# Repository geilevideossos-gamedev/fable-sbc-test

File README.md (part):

# VoxHub CM4 - a Home Assistant voice hub with Claude inside

A single-board computer for home automation that runs **Home Assistant OS** and works as a
**Claude-based voice assistant**: it listens for a wake word, transcribes the request locally, lets Claude
answer and control the home through tool use, and speaks the reply.

**Two identical boards, one Home Assistant for the whole house.** Board 1, the **hub** (upstairs), runs Home
Assistant OS, the Zigbee coordinator and the Claude pipeline. Board 2, the **satellite** (downstairs), runs no Home
Assistant: it gives the hub its wake word, microphones, speaker, mute switch and LEDs over Wi-Fi, and its radio
runs Zigbee router firmware that extends the mesh to the ground floor. Every request of both devices goes through
Claude, knows which room it came from, and is answered on the speaker of the device that heard it.

Everything in this repository is generated from code - schematic, PCB, enclosure, OS image and add-on.

| | |
|---|---|
|  |  |
| carrier with CM4 + heat sink (component side) | enclosure, rear view: USB-C PD in, 2 x USB-A, microSD |

**Showcase animation (shows revision A1, not re-rendered for A2):** [`media/voxhub_showcase.mp4`](media/voxhub_showcase.mp4) (1080p60, 21 s: closed device, exploded
view, orbit, reassembly, turntable) - rendered with Blender from the STEP files of this repository, see [`media/`](media/README.md).

> **Status: revision A2, ready to order fully assembled from JLCPCB, not yet built.** Every part is in stock in
> JLCPCB's assembly library (checked live on 2026-11-12), ERC and DRC pass against JLCPCB's design rules, the order files
> are in [`fab/jlcpcb/`](fab/jlcpcb). Nothing has to be soldered by hand: order the boards, print the enclosure, plug in
> the CM4, screw it together. No hardware exists yet - read the "Open items" in [DECISIONS.md](DECISIONS.md) first.
>
> | Step | Document |
> |---|---|
> | 1. Order 5 PCBs, 2 of them assembled | [`fab/ORDER_GUIDE.md`](fab/ORDER_GUIDE.md) - every option to click, cost estimate |
> | 2. Buy everything that is not on the board | [`fab/SHOPPING_LIST.md`](fab/SHOPPING_LIST.md) - EU shops, part numbers, prices |
> | 3. Print, test, assemble, flash the radio | [`fab/ASSEMBLY_AND_TEST.md`](fab/ASSEMBLY_AND_TEST.md) |
> | 4. Hub + satellite: Claude pipeline, satellite SD card, pairing, rooms, Zigbee router, tests from both rooms | [`fab/ASSEMBLY_AND_TEST.md`, chapter 7](fab/ASSEMBLY_AND_TEST.md#7-two-devices-hub-and-satellite) |

## System overview

| Function | Implementation |
|---|---|
| Compute | Raspberry Pi **Compute Module 4 Lite, wireless** (BCM2711 4x A72, 4 GB) - official HAOS target `rpi4-64` |
| Wi-Fi / Bluetooth | on the CM4: 2.4 + 5 GHz 802.11ac, Bluetooth 5.0 |
| Storage | microSD (push-push socket, card power switched by the module) |
| USB | 2 x USB-A 2.0 host (stacked), USB2514B hub, 1.3 A current-limited per port, ESD protected |
| Microphones | 2 x Infineon IM69D130 PDM MEMS (bottom port), ADAU7002 PDM-to-I2S, hardware mute switch |
| Speaker | MAX98357A I2S class-D, 3.2 W into 4 ohm, JST-PH header, enclosed 3 W speaker with JST-PH plug in the enclosure |
| Zigbee / Thread | RF-star RF-BM-2652P2 (TI CC2652P, +20 dBm) on UART4, flashed from the CM4 with one command |
| Power | USB-C PD sink (CYPD3177): negotiates 9-20 V, then 5 V / 4 A buck (LMR33640) |
| UI | green + blue status LEDs, red mute LED (hard-wired), mute slider on top |
| PCB | 100 x 74 mm, 4 layers, 1.6 mm (JLC04161H-3313), parts on one side + mute switch and three status LEDs on the other |
| Enclosure | 158.8 x 79.2 x 28 mm, two printed parts, no supports |

### Block diagram

```mermaid
flowchart LR
    PD[USB-C PD charger<br/>9-20 V] --> J1[USB-C<br/>receptacle]
    J1 -->|VBUS| BCR[CYPD3177<br/>PD sink controller]
    J1 -->|VBUS| Q1[P-FET<br/>load switch]
    BCR -->|gate| Q1
    Q1 -->|VBUS_SW| BUCK[LMR33640<br/>5 V / 4 A buck]
    BUCK -->|+5V| CM4
    BUCK -->|+5V| SW[2 x TPS2553<br/>port switches]
    BUCK -->|+5V| AMP[MAX98357A<br/>class-D amp]

    subgraph CM4[Raspberry Pi CM4 Lite wireless]
        SOC[BCM2711 + RAM]
        WIFI[Wi-Fi 2.4/5 GHz + BT 5.0]
    end
    CM4 -->|+3V3, 600 mA| LOADS[hub, SD, radio, mics]

    CM4 <-->|SDIO| SD[microSD]
    CM4 <-->|USB 2.0, nEXTRST| HUB[USB2514B hub]
    HUB <--> USBA[2 x USB-A]
    SW -->|VBUS 1.3 A| USBA

    MIC[2 x IM69D130<br/>PDM mics] -->|PDM| ADAU[ADAU7002<br/>PDM to I2S]
    ADAU -->|I2S data| MUTE{{mute switch}}
    MUTE -->|GPIO20| CM4
    CM4 -->|I2S GPIO18/19/21| AMP
    AMP --> SPK[speaker 4 ohm / 3 W]

    CM4 <-->|UART4, boot strap,<br/>reset, JTAG| ZB[RF-BM-2652P2<br/>Zigbee / Thread]
    CM4 -->|GPIO5/6| LED[status LEDs]
    CM4 <-->|I2C1| BCR
```

### Voice pipeline (hub + satellite)

```mermaid
flowchart LR
    subgraph SAT[satellite, downstairs]
        M2[microphones] --> W2[wake word<br/>microWakeWord]
        P2[speaker]
    end
    subgraph HUB[hub, upstairs: Home Assistant OS]
        M1[microphones] --> W1[wake word<br/>microWakeWord]
        P1[speaker]
        S[STT<br/>Whisper, local] -->|text + area of the device| C[Claude<br/>Anthropic integration]
        C <-->|Assist API: intents,<br/>exposed entities| HA[Home Assistant Core]
        G[VoxHub exposure guard:<br/>no locks, no alarms] -.-> HA
        C -->|text, streamed| T[TTS<br/>Piper, local]
    end
    W1 -->|audio after the wake word| S
    W2 -->|ESPHome API, Wi-Fi| S
    T -->|answer| P1
    T -->|answer URL| P2
```

Both devices run Linux Voice Assistant 1.1.18 (`assistant/voxhub_satellite` on the hub, `os/satellite` on the
satellite). Audio stays in the house; only the transcribed request, Claude's instructions, the names and areas of
the devices you expose and the results of Claude's tool calls go to Anthropic. The single-device VoxHub Assistant add-on
of revision A2 still exists for a hub without a satellite (`assistant/README.md`).

### GPIO map (CM4)

| GPIO | Function | Notes |
|---|---|---|
| 2 / 3 | I2C1 SDA / SCL | CYPD3177 PD controller (HPI, 0x08) |
| 5 / 6 | LED green / blue enable | active high, N-FET drivers, 10k pull-downs |
| 8 / 9 | UART4 TX / RX | radio module DIO12 (RX) / DIO13 (TX), 115200 baud, no flow control |
| 10 / 11 | UART4 CTS / RTS | wired to DIO18 / DIO19, not used by the standard firmware |
| 7 / 17 | JTAG TDI / TDO of the radio | DIO17 / DIO16, recovery flashing only |
| 14 / 15 | UART0 TX / RX | debug header (DNP) |
| 16 | amplifier SD_MODE | high = on (left channel) |
| 18 / 19 / 20 / 21 | I2S BCLK / LRCLK / DIN / DOUT | DIN passes through the mute switch |
| 22 / 23 | JTAG TMS / TCK of the radio | recovery flashing only |
| 24 / 25 | radio reset / boot-loader strap | GPIO24 **high = reset** (open-drain FET on RESET, 100k pull-down); GPIO25 low at reset = ROM serial boot loader (DIO15, 2.2k pull-up) |
| 27 | mute sense | high = muted |

## Power budget

5 V rail (buck output 5.02 V nominal, 4.86 .. 5.17 V over tolerance: Vref +-1.5 %, two 1 % resistors), worst case =
everything at its maximum simultaneously:

| Load | Typical | Peak | Basis |
|---|---|---|---|
| CM4 (SoC, RAM, Wi-Fi) | 3.5 W | 7.0 W | CM4 datasheet: 1.4 A typical maximum at 5 V |
| 3.3 V loads via the CM4 regulator (hub 70/150 mA, microSD 50/200 mA, radio 10/85 mA, mics + converter 3 mA, pull-ups 5 mA) | 0.14 A -> 0.5 W | 0.44 A -> 1.6 W | 3.3 V budget 600 mA; 90 % converter efficiency; radio: CC2652P at +20 dBm |
| USB-A ports | 0.5 W | 5.0 W | 2 x 500 mA (hardware limit 1.3 A per port) |
| Speaker amplifier | 0.3 W | 3.6 W | 3.2 W output at 90 % efficiency; speech averages far less |
| LEDs, pull-ups | 0.05 W | 0.1 W | |
| **5 V rail total** | **4.9 W (0.98 A)** | **17.3 W (3.45 A)** | buck rated 4 A |
| Buck + switch losses | 0.5 W | 1.9 W | 92 % at 9 V in, P-FET 70 mOhm, inductor 54 mOhm |
| **At the USB-C connector** | **5.4 W** | **19.2 W** | 9 V: 0.6 A typ / 2.13 A peak - 20 V: 0.27 A typ / 0.96 A peak |

- The PD controller requests **>= 2 A at 9-20 V** (18 W at 9 V). Realistic operation (no bus-powered disks, speech
  rather than sine waves) stays below 12 W. The theoretical simultaneous peak of 19.2 W exceeds an 18 W contract by 7 %:
  use a **27 W or larger** charger (9 V/3 A, or anything offering 12/15/20 V at >= 2 A) if both USB ports feed
  500 mA devices.
- 3.3 V budget: 440 mA peak of the 600 mA the CM4 can supply.
- Chargers without a 9-20 V PD profile are rejected safely: the load switch stays open, the buck stays in UVLO (< 7 V)
  and the red PD-FAULT LED lights.

## Thermal estimate (SoC)

Assumptions: 25 C room, module mounted component-side down in the vented enclosure, 14 x 14 x 7 mm heat sink on the BCM2711
(36 K/W on its own in free convection), heat also spreading through the module PCB and the two mezzanine connectors.
Effective module-level thermal resistance derived from published CM4 measurements (bare module on the IO board:
~25 K rise idle at ~2 W, ~55-60 K at full load): about **12 K/W bare, ~9.5-10 K/W with the heat sink in this enclosure**.

| Operating point | Module power | Estimated SoC temperature | Comment |
|---|---|---|---|
| Idle (HAOS, add-ons idle) | 2.0 W | 25 + 2.0 x 10 = **45 C** | |
| Voice assistant active (wake word on one core, Whisper bursts) | 3.5 W | **60 C** | normal operation |
| All four cores loaded continuously | 6.5 W | 90 C -> **throttles at 80 C** | firmware limits to roughly 5.5 W; only during updates / long local STT |

Conclusion: fine without a fan for the intended workload (LLM in the cloud). For sustained local inference fit the taller
15 x 15 x 9.5 mm heat sink (there are 12.9 mm between the SoC and the base plate, so about 3 mm stay free under it) or add a 30 mm fan to the base vents.
Other parts at peak load: buck IC ~1.1 W (junction about +45 K), inductor 0.7 W, P-FET 0.33 W - all uncritical.
These are estimates, not measurements - verify with `vcgencmd measure_temp` on the first prototype.

## Repository layout

| Path | Contents |
|---|---|
| [`hardware/`](hardware/README.md) | KiCad 9 project (generated), generator scripts, schematic PDF, BOM, Gerbers, drill, pick-and-place, DXF, renders, fab + assembly notes |
| [`fab/`](fab/ORDER_GUIDE.md) | JLCPCB order package (`jlcpcb/`: Gerbers, BOM, CPL, placement report), order guide, shopping list, assembly and test guide |
| [`tools/`](tools/flash_zigbee.sh) | `flash_zigbee.sh --role hub\|satellite`: writes the Zigbee coordinator (hub), the Zigbee router (satellite) or the Thread firmware to the radio module from the CM4; `test/`: radio simulator and test runner |
| [`enclosure/`](enclosure/README.md) | parametric CadQuery source, STL / 3MF / STEP, renders |
| [`os/`](os/README.md) | HAOS board definition, device tree overlay, `build-image.sh` (hub); [`os/satellite/`](os/satellite/README.md): SD card image of the satellite |
| [`assistant/`](assistant/README.md) | Home Assistant add-ons: **VoxHub Satellite** (hub side of the two-device system, exposure guard) and **VoxHub Assistant** (single device) |
| [`media/`](media/README.md) | showcase animation (MP4), still of the exploded view, Blender script and helpers |
| [`DECISIONS.md`](DECISIONS.md) | every design decision with its reasoning, the datasheet verification table, sourcing decisions, open items |
| [`TODO.md`](TODO.md) | progress checklist |

## How to build everything

Prerequisites: Linux, Python >= 3.10, `zip`, Java >= 21 (only for re-running the autorouter), `xvfb` for the
enclosure renders (`sudo apt install zip xvfb`), and KiCad 9 either as the Docker image `kicad/kicad:9.0` or installed
natively (`KICAD_NATIVE=1`; the Python that imports `pcbnew` also needs `numpy` and `shapely`).

```bash
# 1. Hardware: schematic -> ERC -> netlist -> placement -> autoroute -> DRC -> fabrication outputs -> fab/jlcpcb
docker pull kicad/kicad:9.0             # or: export KICAD_NATIVE=1
SKIP_ROUTE=1 hardware/build.sh all      # re-uses the checked-in autorouter session (reproduces the committed board, ~4 min)
# to autoroute again: wget -P hardware https://github.com/freerouting/freerouting/releases/download/v2.0.1/freerouting-2.0.1.jar
#                     hardware/build.sh all
# to refresh stock and prices: python3 hardware/gen/jlc_lookup.py refresh hardware/gen/sourcing_jlc.json

# 2. Enclosure: STL / 3MF / STEP + renders
pip install cadquery
python3 enclosure/voxhub_enclosure.py enclosure
xvfb-run -a python3 enclosure/render.py

# 3. OS image (latest official HAOS + VoxHub configuration)
sudo apt install git curl xz-utils fdisk mtools device-tree-compiler
os/build-image.sh repack --wifi-ssid "MyWifi" --wifi-psk "secret"
#    -> os/output/haos_voxhub-cm4-<version>.img.xz

# 3b. Satellite image (Raspberry Pi OS Lite + Linux Voice Assistant, about 30 minutes)
sudo apt install qemu-user-static binfmt-support parted e2fsprogs openssl
sudo os/satellite/build-satellite-image.sh --wifi-ssid "MyWifi" --wifi-psk "secret-password" --hub 192.168.1.10 --room Downstairs
#    -> os/output/voxhub-satellite-2026-10-06-lva1.1.18.img.xz

# 4. Add-ons: tests (VoxHub Satellite and VoxHub Assistant), container test of VoxHub Satellite (Docker)
pip install -r assistant/requirements-dev.txt
(cd assistant && python3 -m pytest -q)
assistant/tests/container/run_addon_test.sh

# 4b. Radio flashing script against the simulated radio (about 17 minutes)
sudo apt install python3-serial python3-intelhex
sudo tools/test/run_flash_tests.sh

# 5. Showcase animation (Blender 4.2 - 4.5, headless; a little over 3 hours on 4 CPU cores)
pip install cadquery pymupdf pillow numpy && sudo apt install ffmpeg
BLENDER=/path/to/blender media/build_showcase.sh
```

Then: order the boards (`fab/ORDER_GUIDE.md`), buy the rest (`fab/SHOPPING_LIST.md`), print `enclosure/voxhub_shell.3mf` and
`voxhub_base.3mf`, test and assemble (`fab/ASSEMBLY_AND_TEST.md`), flash the image, flash the radio (`tools/flash_zigbee.sh`),
add this repository as an add-on repository in Home Assistant (until the two-device version is merged into `main`:
`https://github.com/geilevideossos-gamedev/fable-sbc-test#claude/gallant-hamilton-kojnjj`) and install **VoxHub
Satellite**; for the second board
write the satellite image and follow `fab/ASSEMBLY_AND_TEST.md`, chapter 7.

## Cost summary

**Parts on the board**, JLCPCB prices of 2026-11-12 (USD, without tax, PCB, assembly fees and shipping).
Line by line: [`hardware/outputs/bom.csv`](hardware/outputs/bom.csv).

| Group | Lines | Placements | 1 board | per board at 100 |
|---|---|---|---|---|
| ICs and radio module (RF-BM-2652P2 alone: 6.63 / 5.56) | 8 | 11 | 20.85 | 15.11 |
| Connectors, slide switch, SMT spacers | 7 | 11 | 10.44 | 7.48 |
| Inductor, crystal, microphones | 3 | 4 | 6.48 | 4.23 |
| Capacitors | 11 | 49 | 2.78 | 2.21 |
| Diodes, LEDs, transistors | 9 | 14 | 1.18 | 0.96 |
| Resistors | 15 | 47 | 0.03 | 0.03 |
| **PCB assembly parts** | **53 (+2 DNP)** | **136** | **41.78** | **30.03** |

**Everything else for one device**, EU shops, prices of 2026-11-12 including VAT (EUR).
Line by line: [`hardware/outputs/bom_system.csv`](hardware/outputs/bom_system.csv) and [`fab/SHOPPING_LIST.md`](fab/SHOPPING_LIST.md).

| Item | EUR |
|---|---|
| Raspberry Pi CM4 Lite 4 GB wireless (CM4104000) | 105.83 |
| microSD card 64 GB, endurance type | 28.90 |
| USB-C PD charger 30 W and cable | 22.38 |
| Speaker with JST-PH plug, heat sink, screws, feet, foam | 18.39 |
| Shipping of two parcels to Austria | 12.90 |
| **One device without the board** | **188.40** |

**Hub + satellite** (the satellite with a 1 GB module, CM4101000, 50.82 EUR, and a 32 GB card): **286.90 EUR**
delivered for both devices without the boards, 66.01 EUR less than two hubs - [`fab/SHOPPING_LIST.md`, section
8](fab/SHOPPING_LIST.md#8-two-device-system-satellite-variant-and-combined-basket-hub--satellite).

**The JLCPCB order** (5 PCBs, 2 of them assembled on both sides, parts, shipping, import VAT) is estimated in
[`fab/ORDER_GUIDE.md`](fab/ORDER_GUIDE.md).

- The same JLCPCB parts cost 41.78 USD where the DigiKey parts of revision A1 cost 74.79 USD; the radio module alone
  went from 11.47 to 6.63 USD.
- Thin stock at JLCPCB on the day of the check: ADAU7002ACBZ-R7 (104), Wurth 61400826021 (116), RF-BM-2652P2 (126).
  The order guide says how to reserve them; the BOM names the alternates. Details in
  [DECISIONS.md, section 10](DECISIONS.md#10-sourcing-jlcpcb--lcsc-live-check-2026-11-12-digikey-2026-11-11-as-the-second-source).
- In a Standard PCBA order JLCPCB charges the same feeder fee for every part type, Basic or Extended, so the 32 Extended
  lines cost nothing extra compared with Basic parts; what counts is the number of BOM lines (53).

## Verification summary

| Check | Result | Evidence |
|---|---|---|
| ERC (kicad-cli 9.0.9) | 0 errors, 0 warnings | `hardware/outputs/erc.rpt` |
| Netlist equals the code model | 150 components / 100 nets; schematic parity 0 issues | `hardware/gen/model_netlist.json`, `hardware/outputs/drc.rpt` |
| DRC with schematic parity and JLCPCB's rules (kicad-cli 9.0.9) | 0 violations, 0 unconnected pads, 0 parity issues; two library-comparison checks waived (5 warnings, explained in `hardware/README.md`) | `hardware/outputs/drc.rpt`, `drc_waived_checks_enabled.rpt`, `hardware/voxhub.kicad_dru` |
| Current paths | narrowest copper of every high-current path measured: all as wide as designed (1.2 to 1.6 mm; the remaining necks are the 0.6 mm pads of the connector and of the regulator) | `hardware/outputs/power_paths.txt` |
| Vias and pads | no via in or touching a pad other than the exposed pad of an IC | `hardware/outputs/via_in_pad.txt` |
| USB 2.0 | upstream pair coupled, 0.14 / 0.16 mm = 89.96 ohm in JLCPCB's impedance calculator; pad-to-pad skew 0.00 / 0.00 / 0.00 mm (upstream / port 1 / port 2), limit 3.8 mm; no vias, no stubs | `hardware/outputs/usb_impedance.txt`, `routing_stats.txt`, DECISIONS.md section 6a |
| CM4 socket strips | no copper of another net in Hirose's restricted strips | `hardware/outputs/df40_strips.txt` |
| Assembly data | 135 of 136 placements fitted to JLCPCB's own footprint of the part (position, rotation, polarity); the last one is the hand-soldered USB-A connector | `fab/jlcpcb/placement_report.csv` |
| Parts vs. datasheets | 34 rows: 31 "verified against datasheet" with source (seven of them still read from distributor copies of the manufacturer PDF), 2 rows with shop dimensions only (speaker, heat sink), 1 row of generic passives / standard footprints not individually verified | `DECISIONS.md` section 9 and decision logs |
| PCB render | kicad-cli 3D renders | `hardware/outputs/render_*.png` |
| Enclosure fit | part dimensions from the manufacturer drawings; 0 mm^3 interference PCB assembly vs. printed parts | `enclosure/voxhub_enclosure.py`, `enclosure/README.md` |
| Power budget / thermal estimate | above | |
| Sourcing | every BOM line in stock in JLCPCB's assembly library on 2026-11-12 (three lines below 200 pieces); DigiKey data of 2026-11-11 as the second source | `hardware/outputs/bom.csv`, `hardware/gen/sourcing_jlc.json` |
| Radio flashing | one command; run end to end against a simulated radio with the real flashing tool, dry run in this repository; not on hardware | `tools/flash_zigbee.sh`, `fab/ASSEMBLY_AND_TEST.md` |
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
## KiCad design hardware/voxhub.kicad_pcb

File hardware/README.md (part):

# Hardware: VoxHub CM4 carrier, revision A2

KiCad 9 project, **generated entirely from code** (`gen/`). Do not edit the `.kicad_sch` / `.kicad_pcb` files
by hand - change the generator and run `./build.sh`.

Revision A2 is the revision that is ordered fully assembled from JLCPCB. The order files are in
[`../fab/jlcpcb/`](../fab/jlcpcb), the ordering steps in [`../fab/ORDER_GUIDE.md`](../fab/ORDER_GUIDE.md), what changed
from A1 and why in the A2 log of [`../DECISIONS.md`](../DECISIONS.md).

## Contents

| Path | What |
|---|---|
| `voxhub.kicad_pro`, `voxhub.kicad_sch` + 5 sub-sheets, `voxhub.kicad_pcb` | the KiCad project |
| `voxhub.kicad_dru` | JLCPCB limits that KiCad's board setup cannot express (component holes, pad to pad) |
| `voxhub.kicad_sym`, `voxhub.pretty/` | project symbol / footprint libraries (generated) |
| `3dmodels/` | STEP models used by the footprints (KiCad library copies + simple stand-ins) |
| `gen/design.py` | **the circuit**: every part, value and net |
| `gen/kisch.py`, `gen/sexpr.py` | schematic writer |
| `gen/parts.py` | part catalogue: one entry per purchasable part |
| `gen/jlc_lookup.py`, `gen/sourcing_jlc.json`, `gen/jlc_footprints.json` | live lookups in JLCPCB's assembly library and at LCSC; the stored result (LCSC number, library type, stock, prices); JLCPCB's own footprints of every part |
| `gen/sourcing.py`, `gen/sourcing_live.json`, `gen/make_bom.py` | second sources, DigiKey data of 2026-11-11, system parts with their EU shop, BOM generator |
| `gen/make_footprints.py`, `gen/make_3dmodels.py` | project footprints and coloured stand-in models |
| `gen/prewire.py` | **hand-designed copper**: PD input, load switch, buck stage, USB port supplies, all six USB data lines; stack-up and USB geometry |
| `gen/build_pcb.py` | placement, silkscreen legends, pre-wired copper, power fan-out, keep-outs, DSN export, import, patch router, repair, USB length measurement |
| `gen/postroute.sh` | iterate DRC -> repair -> patch until clean |
| `gen/check_power.py`, `gen/check_df40.py`, `gen/check_vias.py` | build gates: narrowest copper of the high-current paths; foreign copper in the CM4 socket strips; vias in or touching a pad |
| `gen/jlc_impedance.py` | asks JLCPCB's impedance calculator for the USB geometry |
| `gen/make_jlc.py` | JLCPCB BOM, CPL and placement report |
| `gen/routed/voxhub.ses` | autorouter session (Freerouting 2.0.1) the committed board was built from |
| `gen/placement.json` | final part positions (also drives the enclosure model) |
| `outputs/` | reports and fabrication data (below) |

### `outputs/`

| File | Purpose |
|---|---|
| `voxhub_schematic.pdf` | schematic, 6 pages |
| `erc.rpt`, `drc.rpt` | kicad-cli reports: **0 ERC violations, 0 DRC violations, 0 unconnected, 0 parity issues** |
| `drc_waived_checks_enabled.rpt` | the same DRC with the two waived checks switched on (5 warnings, explained below) |
| `power_paths.txt` | narrowest copper of every high-current path against its requirement |
| `df40_strips.txt` | copper inside Hirose's restricted strips of the CM4 sockets (own net / other net) |
| `via_in_pad.txt` | vias whose land overlaps an SMD pad (allowed only inside the exposed pad of an IC) |
| `usb_impedance.txt` | USB track geometry in JLCPCB's impedance calculator |
| `routing_stats.txt` | track / via counts; USB lines: pad-to-pad length and skew, the pads each line runs through, copper that is not on that path; SD / I2S / PDM lengths |
| `gerbers/` + `voxhub_gerbers.zip` | Gerbers with Protel extensions: F / In1 / In2 / B copper, mask, paste, silk, Edge.Cuts; Excellon PTH + NPTH drill, drill maps, job file (`../fab/jlcpcb/gerbers.zip` is the same set without maps and job file) |
| `voxhub_pos.csv` | pick-and-place as KiCad exports it (both sides, DNP parts excluded); for JLCPCB use `../fab/jlcpcb/cpl_jlcpcb.csv` |
| `bom.csv`, `bom_summary.json` | PCB assembly BOM: MPN, LCSC number, JLCPCB library type, JLCPCB and LCSC stock, JLCPCB prices at 1 / 10 / 100 (live, 2026-11-12), DigiKey second source (2026-11-11), other alternates |
| `bom_system.csv` | module, speaker, heat sink, screws, SD card, charger with EU shop and price |
| `voxhub_outline.dxf`, `mechanical_positions.csv` | mechanical outline: board edge, mounting holes, CM4 holes / outline, microphone ports, connector envelopes |
| `voxhub_pcb.step` | 3D model of the assembled board |
| `pcb_layers/voxhub.pdf` | layer plots |
| `render_top.png`, `render_bottom.png`, `render_iso.png` | kicad-cli 3D renders |

## Rebuilding

```bash
docker pull kicad/kicad:9.0                # KiCad 9.0.9 was used
wget -P hardware https://github.com/freerouting/freerouting/releases/download/v2.0.1/freerouting-2.0.1.jar
SKIP_ROUTE=1 hardware/build.sh all         # schematic -> ERC -> netlist -> place -> import -> patch -> DRC -> outputs -> fab/jlcpcb
hardware/build.sh all                      # same, but re-runs the autorouter first (Java >= 21)
```

Single steps: `hardware/build.sh sch | pcb | route | outputs`.

| Environment variable | Meaning |
|---|---|
| `KICAD_IMAGE` | Docker image with KiCad 9 (default `kicad/kicad:9.0`). `shapely` is installed into the container with pip when it is missing |
| `KICAD_NATIVE=1` | use `kicad-cli` and `pcbnew` of the host instead of Docker. The build picks the first of `$KICAD_PYTHON`, `python3`, `python3.12`, `python3.11` that imports `pcbnew`, `numpy` and `shapely` |
| `FREEROUTING` | path of the Freerouting jar (default `hardware/freerouting-2.0.1.jar`) |
| `SKIP_ROUTE=1` | re-use the committed autorouter session |

The host needs `python3` and `zip` (the archives are packed on the host; the script checks for `zip` first), and
`docker` unless `KICAD_NATIVE=1` is set.

`SKIP_ROUTE=1` re-uses the committed autorouter session and reproduces the committed board exactly (the patch
router is deterministic). Freerouting 2.0.1 with one thread produced the same session in every run here, but that is not
guaranteed on another machine or JRE. Two quirks the build works around: it sometimes exits with an empty session file
after routing (the build starts it up to three times and checks the file), and it keeps a `freerouting.json` in the
temp directory (each run gets its own).

Scripts that are run by hand:

| Command | What it does |
|---|---|
| `python3 gen/jlc_lookup.py refresh gen/sourcing_jlc.json` | reads stock, library type and prices of every BOM line live from JLCPCB and LCSC |
| `python3 gen/jlc_lookup.py footprints gen/sourcing_jlc.json gen/jlc_footprints.json` | fetches JLCPCB's footprint of every LCSC part (needed after a part change) |
| `python3 gen/jlc_lookup.py search "<keyword>"`, `... code C12345` | search the assembly library; full record of one part |
| `python3 gen/jlc_impedance.py outputs/usb_impedance.txt` | USB geometry of `prewire.py` in JLCPCB's impedance calculator |
| `python3 gen/check_power.py voxhub.kicad_pcb outputs/power_paths.txt` | current-path widths (run by `build.sh outputs`) |
| `python3 gen/check_df40.py voxhub.kicad_pcb outputs/df40_strips.txt` | CM4 socket strips (run by `build.sh outputs`) |
| `python3 gen/check_vias.py voxhub.kicad_pcb outputs/via_in_pad.txt` | vias against pads (run by `build.sh outputs`) |
| `python3 gen/make_jlc.py voxhub.kicad_pcb gen/sourcing_jlc.json gen/jlc_footprints.json ../fab/jlcpcb` | JLCPCB BOM, CPL, placement report (run by `build.sh outputs`) |

How the board is produced:

1. `design.py` writes the schematic; `kicad-cli sch erc` must pass; the KiCad netlist is compared pin by pin with the code model.
2. `build_pcb.py place`: fixed positions for connectors / ICs / mechanics and for the hand-placed power stage and USB parts,
   a greedy "nearest free spot to the pad it talks to" placer for the other passives; outline; keep-outs; silkscreen
   legends by an occupancy search; then the **pre-wired copper of `prewire.py`** (locked), the scripted fan-out of the
   remaining GND / +5V pads to the inner planes (never a via in or touching a lead pad), the fixed escape pattern of the
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
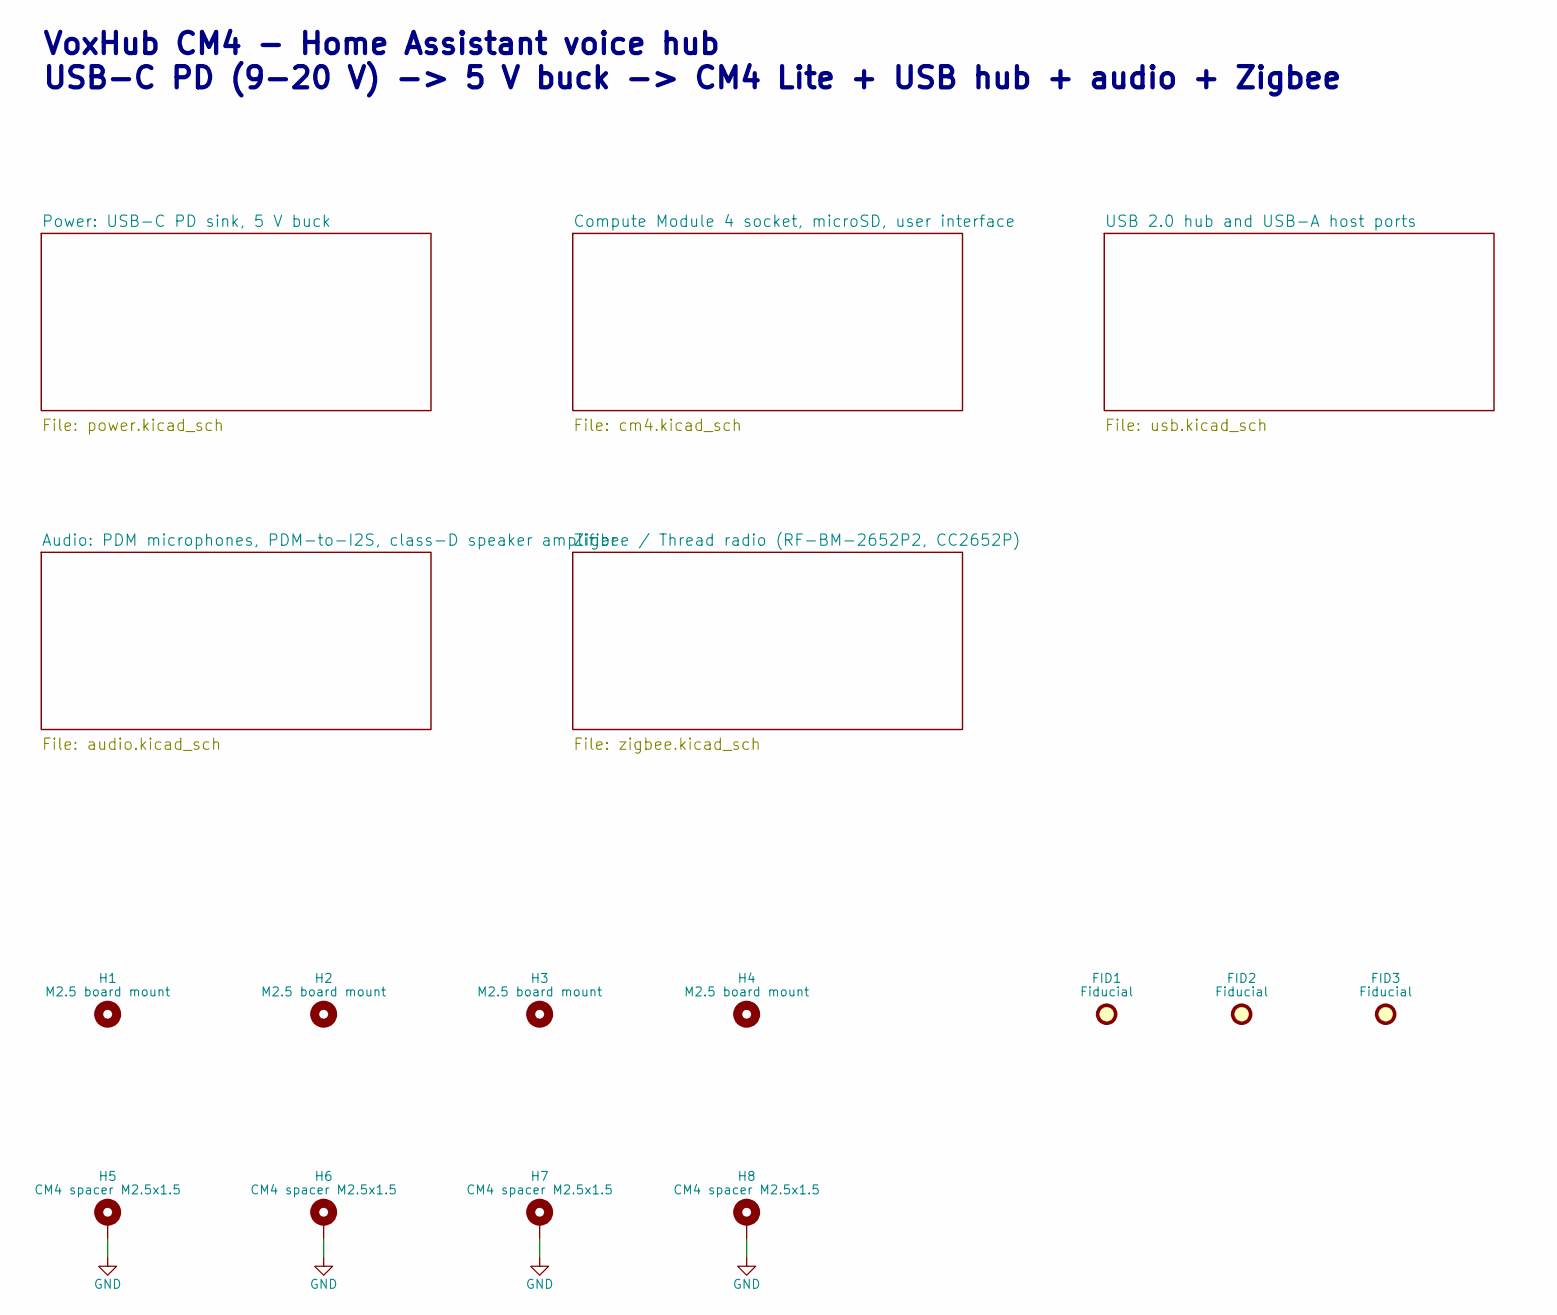
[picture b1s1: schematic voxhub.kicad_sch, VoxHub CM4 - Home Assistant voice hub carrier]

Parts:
FID1, FID2, FID3: Fiducial; Fiducial_1mm_Mask2mm; PartDescription Fiducial
H1, H2, H3, H4: M2.5 board mount; MountingHole_2.7mm_M2.5; PartDescription PCB mounting hole
H5, H6, H7, H8: CM4 spacer M2.5x1.5; Mounting_Wuerth_WA-SMSI-M2.5_H1.5mm_9774015151; MPN 9774015151R

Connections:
GND: H5.1, H6.1, H7.1, H8.1; also elsewhere on the board

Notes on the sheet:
VoxHub CM4 - Home Assistant voice hub USB-C PD (9-20 V) -> 5 V buck -> CM4 Lite + USB hub + audio + Zigbee

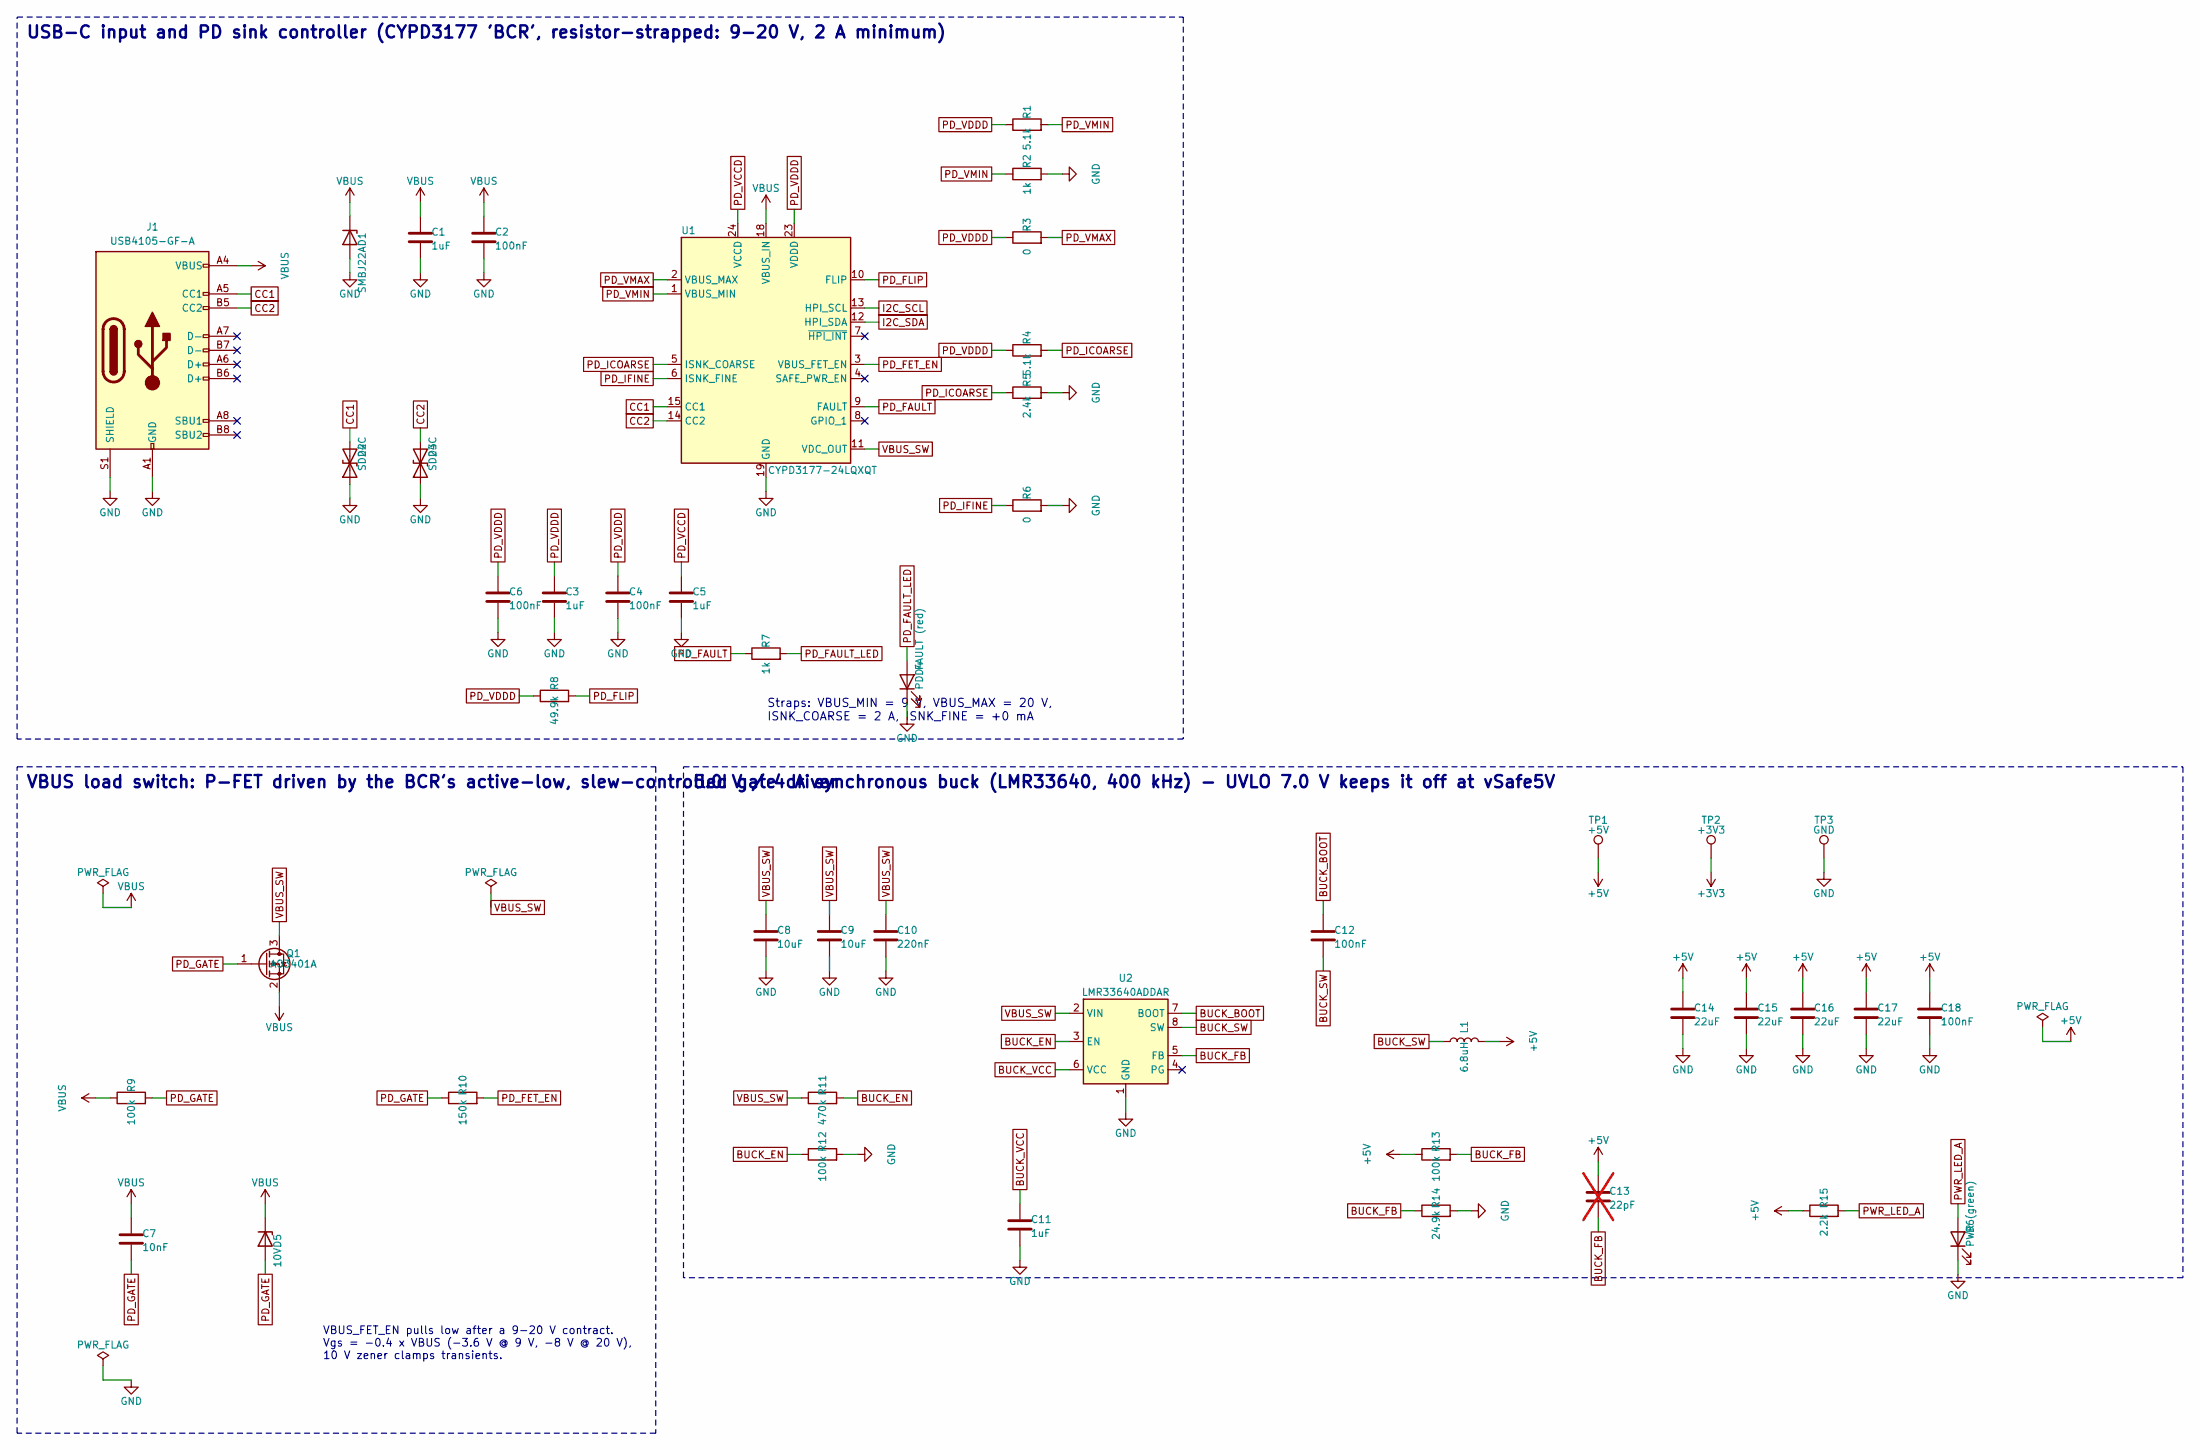
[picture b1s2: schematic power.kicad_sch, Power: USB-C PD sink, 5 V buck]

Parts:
C1: 1uF; C_0603_1608Metric; MPN CL10A105KB8NNNC
C2: 100nF; C_0603_1608Metric; MPN CC0603KRX7R9BB104
C3, C5, C11: 1uF; C_0603_1608Metric; MPN CL10B105KA8NNNC
C4, C6, C12, C18: 100nF; C_0402_1005Metric; MPN CL05B104KO5NNNC
C7: 10nF; C_0402_1005Metric; MPN CL05B103KB5NNNC
C8, C9: 10uF; C_1206_3216Metric; MPN CL31B106KBHNNNE
C10: 220nF; C_0603_1608Metric; MPN GRM188R71H224KAC4D
C13: 22pF; C_0402_1005Metric; MPN 0402CG220J500NT; not fitted
C14, C15, C16, C17: 22uF; C_1206_3216Metric; MPN CL31A226KAHNNNE
D1: SMBJ22A; D_SMB; MPN SMBJ22A
D2, D3: SD24C; D_SOD-323; MPN SD24C-01FTG
D4: PD FAULT (red); LED_0603_1608Metric; MPN LTST-C191KRKT
D5: 10V; D_SOD-323; MPN MM3Z10VT1G
D6: PWR (green); LED_0603_1608Metric; MPN 150060VS75000
J1: USB4105-GF-A; USB_C_Receptacle_GCT_USB4105-xx-A_16P_TopMnt_Horizontal; MPN USB4105-GF-A
L1: 6.8uH; L_Bourns_SRP7028A_7.3x6.6mm; MPN SLO0630H6R8MTT
Q1: AO3401A; SOT-23; MPN AO3401A
R1, R4: 5.1k; R_0402_1005Metric; MPN 0402WGF5101TCE
R2, R7: 1k; R_0402_1005Metric; MPN 0402WGF1001TCE
R3, R6: 0; R_0402_1005Metric; MPN 0402WGF0000TCE
R5: 2.4k; R_0402_1005Metric; MPN 0402WGF2401TCE
R8: 49.9k; R_0402_1005Metric; MPN 0402WGF4992TCE
R9, R12, R13: 100k; R_0402_1005Metric; MPN 0402WGF1003TCE
R10: 150k; R_0402_1005Metric; MPN 0402WGF1503TCE
R11: 470k; R_0402_1005Metric; MPN 0402WGF4703TCE
R14: 24.9k; R_0402_1005Metric; MPN 0402WGF2492TCE
R15: 2.2k; R_0402_1005Metric; MPN 0402WGF2201TCE
TP1: +5V; TestPoint_Pad_D1.5mm; PartDescription Test pad (no part)
TP2: +3V3; TestPoint_Pad_D1.5mm; PartDescription Test pad (no part)
TP3: GND; TestPoint_Pad_D1.5mm; PartDescription Test pad (no part)
U1: CYPD3177-24LQXQT; QFN-24-1EP_4x4mm_P0.5mm_EP2.75x2.75mm; MPN CYPD3177-24LQXQT
U2: LMR33640ADDAR; Texas_HSOP-8-1EP_3.9x4.9mm_P1.27mm_ThermalVias; MPN LMR33640ADDAR

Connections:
+3V3: TP2.1; also elsewhere on the board
+5V: C13.1, C14.1, C15.1, C16.1, C17.1, C18.1, L1.2, R13.1, R15.1, TP1.1; also elsewhere on the board
BUCK_BOOT: C12.1, U2.7 (BOOT)
BUCK_EN: R11.2, R12.1, U2.3 (EN)
BUCK_FB: C13.2, R13.2, R14.1, U2.5 (FB)
BUCK_SW: C12.2, L1.1, U2.8 (SW)
BUCK_VCC: C11.1, U2.6 (VCC)
CC1: D2.2 (A2), J1.A5 (CC1), U1.15 (CC1)
CC2: D3.2 (A2), J1.B5 (CC2), U1.14 (CC2)
GND: C1.2, C2.2, C3.2, C4.2, C5.2, C6.2, C8.2, C9.2, C10.2, C11.2, C14.2, C15.2, C16.2, C17.2, C18.2, D1.2 (A), D2.1 (A1), D3.1 (A1), D4.1 (K), D6.1 (K), J1.A1 (GND), J1.A12 (GND), J1.B1 (GND), J1.B12 (GND), J1.S1 (SHIELD), R2.2, R5.2, R6.2, R12.2, R14.2, TP3.1, U1.19 (GND), U1.22 (GND), U1.25 (GND), U2.1 (GND), U2.9 (GND); also elsewhere on the board
I2C_SCL: U1.13 (HPI_SCL); also elsewhere on the board
I2C_SDA: U1.12 (HPI_SDA); also elsewhere on the board
PD_FAULT: R7.1, U1.9 (FAULT)
PD_FAULT_LED: D4.2 (A), R7.2
PD_FET_EN: R10.2, U1.3 (VBUS_FET_EN)
PD_FLIP: R8.2, U1.10 (FLIP)
PD_GATE: C7.2, D5.2 (A), Q1.1 (G), R9.2, R10.1
PD_ICOARSE: R4.2, R5.1, U1.5 (ISNK_COARSE)
PD_IFINE: R6.1, U1.6 (ISNK_FINE)
PD_VCCD: C5.1, U1.24 (VCCD)
PD_VDDD: C3.1, C4.1, C6.1, R1.1, R3.1, R4.1, R8.1, U1.23 (VDDD)
PD_VMAX: R3.2, U1.2 (VBUS_MAX)
PD_VMIN: R1.2, R2.1, U1.1 (VBUS_MIN)
PWR_LED_A: D6.2 (A), R15.2
VBUS: C1.1, C2.1, C7.1, D1.1 (K), D5.1 (K), J1.A4 (VBUS), J1.A9 (VBUS), J1.B4 (VBUS), J1.B9 (VBUS), Q1.2 (S), R9.1, U1.18 (VBUS_IN)
VBUS_SW: C8.1, C9.1, C10.1, Q1.3 (D), R11.1, U1.11 (VDC_OUT), U2.2 (VIN)

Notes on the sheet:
USB-C input and PD sink controller (CYPD3177 'BCR', resistor-strapped: 9-20 V, 2 A minimum)
Straps: VBUS_MIN = 9 V, VBUS_MAX = 20 V, ISNK_COARSE = 2 A, ISNK_FINE = +0 mA
VBUS load switch: P-FET driven by the BCR's active-low, slew-controlled gate driver
VBUS_FET_EN pulls low after a 9-20 V contract. Vgs = -0.4 x VBUS (-3.6 V @ 9 V, -8 V @ 20 V), 10 V zener clamps transients.
5.0 V / 4 A synchronous buck (LMR33640, 400 kHz) - UVLO 7.0 V keeps it off at vSafe5V

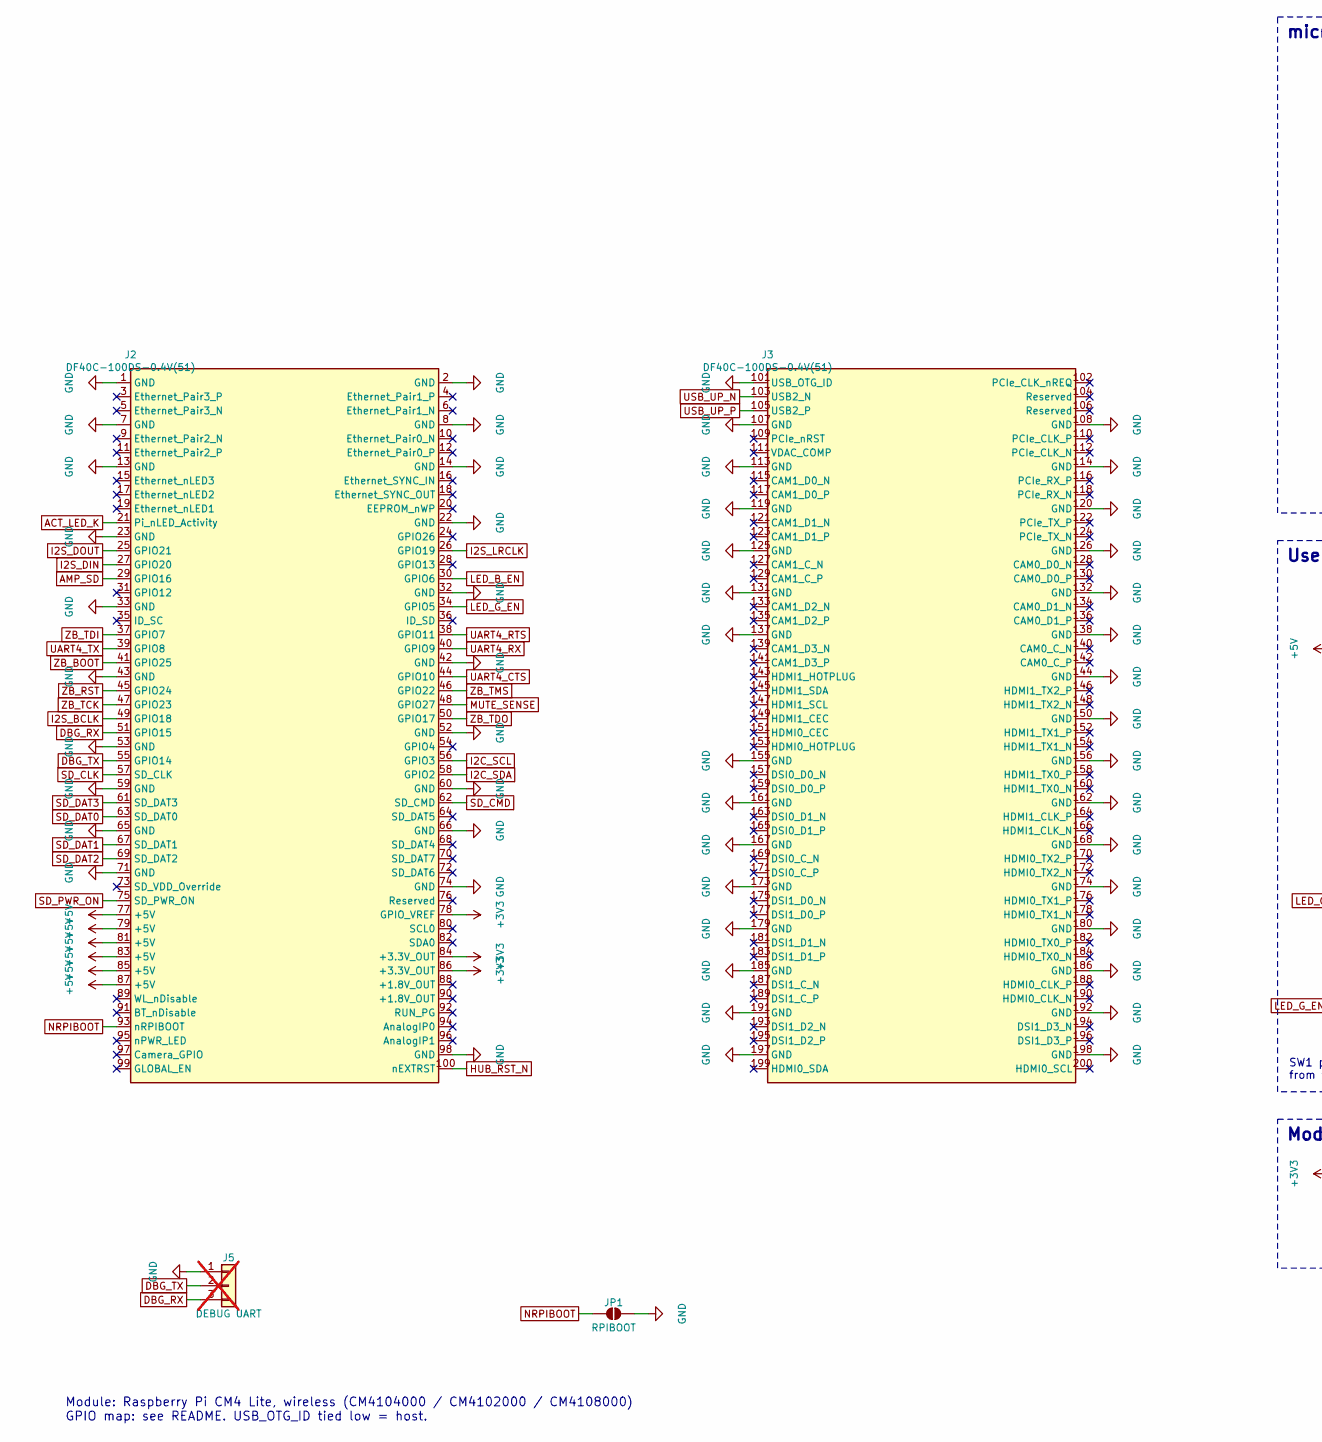
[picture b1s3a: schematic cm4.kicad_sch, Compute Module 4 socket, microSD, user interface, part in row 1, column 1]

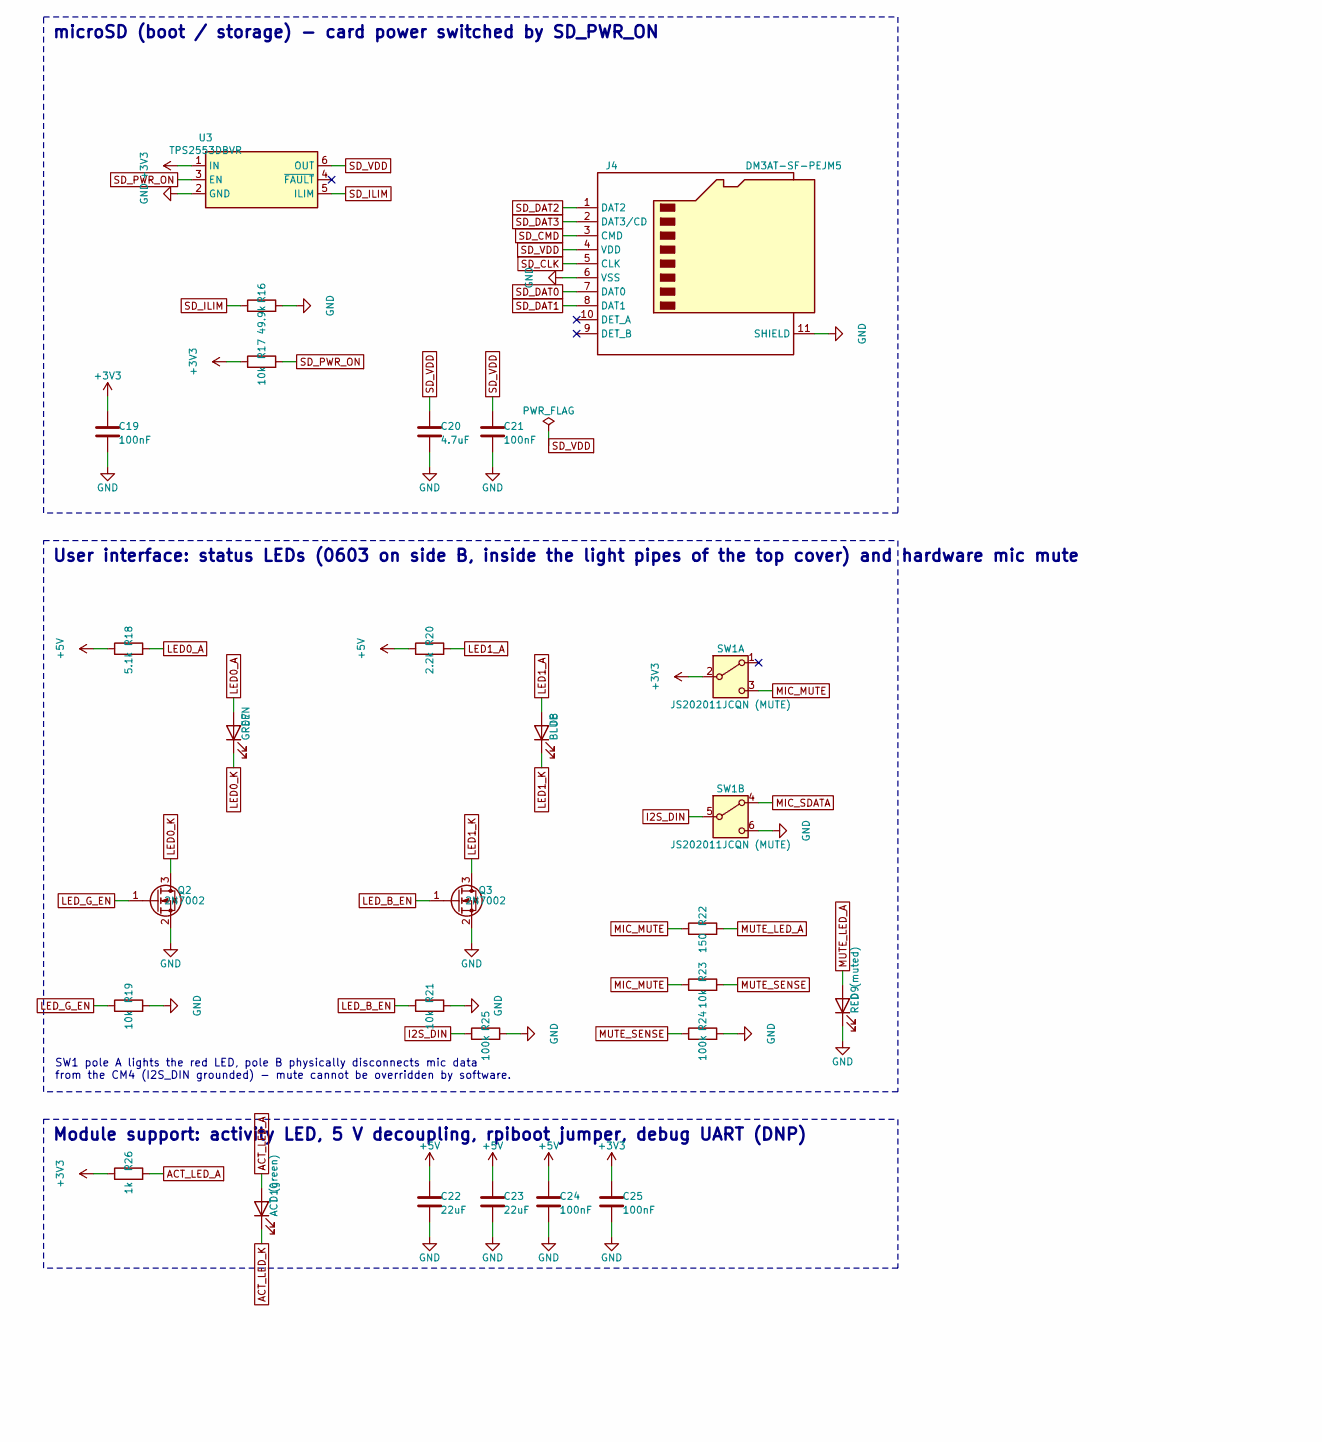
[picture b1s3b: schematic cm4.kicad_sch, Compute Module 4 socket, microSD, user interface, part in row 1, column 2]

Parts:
C19, C21, C24, C25: 100nF; C_0402_1005Metric; MPN CL05B104KO5NNNC
C20: 4.7uF; C_0603_1608Metric; MPN CL10A475KA8NQNC
C22, C23: 22uF; C_1206_3216Metric; MPN CL31A226KAHNNNE
D7: GREEN; LED_0603_1608Metric; MPN KT-0603G
D8: BLUE; LED_0603_1608Metric; MPN KT-0603B
D9: RED (muted); LED_0603_1608Metric; MPN LTST-C191KRKT
D10: ACT (green); LED_0603_1608Metric; MPN 150060VS75000
J2: DF40C-100DS-0.4V(51); CM4_J1_DF40C-100DS; MPN DF40C-100DS-0.4V(51)
J3: DF40C-100DS-0.4V(51); CM4_J2_DF40C-100DS; MPN DF40C-100DS-0.4V(51)
J4: DM3AT-SF-PEJM5; microSD_HC_Hirose_DM3AT-SF-PEJM5; MPN DM3AT-SF-PEJM5
J5: DEBUG UART; PinHeader_1x03_P2.54mm_Vertical; MPN 61300311121; not fitted
JP1: RPIBOOT; SolderJumper-2_P1.3mm_Open_RoundedPad1.0x1.5mm; PartDescription Solder jumper (no part)
Q2, Q3: 2N7002; SOT-23; MPN 2N7002,215
R16: 49.9k; R_0402_1005Metric; MPN 0402WGF4992TCE
R17, R19, R21, R23: 10k; R_0402_1005Metric; MPN 0402WGF1002TCE
R18: 5.1k; R_0402_1005Metric; MPN 0402WGF5101TCE
R20: 2.2k; R_0402_1005Metric; MPN 0402WGF2201TCE
R22: 150; R_0402_1005Metric; MPN 0402WGF1500TCE
R24, R25: 100k; R_0402_1005Metric; MPN 0402WGF1003TCE
R26: 1k; R_0402_1005Metric; MPN 0402WGF1001TCE
SW1: JS202011JCQN (MUTE); SW_DPDT_CK_JS202011JCQN; MPN JS202011JCQN
U3: TPS2553DBVR; SOT-23-6; MPN TPS2553DBVR

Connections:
+3V3: C19.1, C25.1, J2.78 (GPIO_VREF), J2.84 (+3.3V_OUT), J2.86 (+3.3V_OUT), R17.1, R26.1, SW1.2 (B), U3.1 (IN); also elsewhere on the board
+5V: C22.1, C23.1, C24.1, J2.77 (+5V), J2.79 (+5V), J2.81 (+5V), J2.83 (+5V), J2.85 (+5V), J2.87 (+5V), R18.1, R20.1; also elsewhere on the board
ACT_LED_A: D10.2 (A), R26.2
ACT_LED_K: D10.1 (K), J2.21 (Pi_nLED_Activity)
AMP_SD: J2.29 (GPIO16); also elsewhere on the board
DBG_RX: J2.51 (GPIO15), J5.3
DBG_TX: J2.55 (GPIO14), J5.2
GND: C19.2, C20.2, C21.2, C22.2, C23.2, C24.2, C25.2, D9.1 (K), J2.1 (GND), J2.2 (GND), J2.7 (GND), J2.8 (GND), J2.13 (GND), J2.14 (GND), J2.22 (GND), J2.23 (GND), J2.32 (GND), J2.33 (GND), J2.42 (GND), J2.43 (GND), J2.52 (GND), J2.53 (GND), J2.59 (GND), J2.60 (GND), J2.65 (GND), J2.66 (GND), J2.71 (GND), J2.74 (GND), J2.98 (GND), J3.101 (USB_OTG_ID), J3.107 (GND), J3.108 (GND), J3.113 (GND), J3.114 (GND), J3.119 (GND), J3.120 (GND), J3.125 (GND), J3.126 (GND), J3.131 (GND), J3.132 (GND), J3.137 (GND), J3.138 (GND), J3.144 (GND), J3.150 (GND), J3.155 (GND), J3.156 (GND), J3.161 (GND), J3.162 (GND), J3.167 (GND), J3.168 (GND), J3.173 (GND), J3.174 (GND), J3.179 (GND), J3.180 (GND), J3.185 (GND), J3.186 (GND), J3.191 (GND), J3.192 (GND), J3.197 (GND), J3.198 (GND), J4.6 (VSS), J4.11 (SHIELD), J5.1, JP1.2 (B), Q2.2 (S), Q3.2 (S), R16.2, R19.2, R21.2, R24.2, R25.2, SW1.6 (C), U3.2 (GND); also elsewhere on the board
HUB_RST_N: J2.100 (nEXTRST); also elsewhere on the board
I2C_SCL: J2.56 (GPIO3); also elsewhere on the board
I2C_SDA: J2.58 (GPIO2); also elsewhere on the board
I2S_BCLK: J2.49 (GPIO18); also elsewhere on the board
I2S_DIN: J2.27 (GPIO20), R25.1, SW1.5 (B)
I2S_DOUT: J2.25 (GPIO21); also elsewhere on the board
I2S_LRCLK: J2.26 (GPIO19); also elsewhere on the board
LED0_A: D7.2 (A), R18.2
LED0_K: D7.1 (K), Q2.3 (D)
LED1_A: D8.2 (A), R20.2
LED1_K: D8.1 (K), Q3.3 (D)
LED_B_EN: J2.30 (GPIO6), Q3.1 (G), R21.1
LED_G_EN: J2.34 (GPIO5), Q2.1 (G), R19.1
MIC_MUTE: R22.1, R23.1, SW1.3 (C)
MIC_SDATA: SW1.4 (A); also elsewhere on the board
MUTE_LED_A: D9.2 (A), R22.2
MUTE_SENSE: J2.48 (GPIO27), R23.2, R24.1
NRPIBOOT: J2.93 (nRPIBOOT), JP1.1 (A)
SD_CLK: J2.57 (SD_CLK), J4.5 (CLK)
SD_CMD: J2.62 (SD_CMD), J4.3 (CMD)
SD_DAT0: J2.63 (SD_DAT0), J4.7 (DAT0)
SD_DAT1: J2.67 (SD_DAT1), J4.8 (DAT1)
SD_DAT2: J2.69 (SD_DAT2), J4.1 (DAT2)
SD_DAT3: J2.61 (SD_DAT3), J4.2 (DAT3/CD)
SD_ILIM: R16.1, U3.5 (ILIM)
SD_PWR_ON: J2.75 (SD_PWR_ON), R17.2, U3.3 (EN)
SD_VDD: C20.1, C21.1, J4.4 (VDD), U3.6 (OUT)
UART4_CTS: J2.44 (GPIO10); also elsewhere on the board
UART4_RTS: J2.38 (GPIO11); also elsewhere on the board
UART4_RX: J2.40 (GPIO9); also elsewhere on the board
UART4_TX: J2.39 (GPIO8); also elsewhere on the board
USB_UP_N: J3.103 (USB2_N); also elsewhere on the board
USB_UP_P: J3.105 (USB2_P); also elsewhere on the board
ZB_BOOT: J2.41 (GPIO25); also elsewhere on the board
ZB_RST: J2.45 (GPIO24); also elsewhere on the board
ZB_TCK: J2.47 (GPIO23); also elsewhere on the board
ZB_TDI: J2.37 (GPIO7); also elsewhere on the board
ZB_TDO: J2.50 (GPIO17); also elsewhere on the board
ZB_TMS: J2.46 (GPIO22); also elsewhere on the board

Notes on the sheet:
Module: Raspberry Pi CM4 Lite, wireless (CM4104000 / CM4102000 / CM4108000) GPIO map: see README. USB_OTG_ID tied low = host.
microSD (boot / storage) - card power switched by SD_PWR_ON
User interface: status LEDs (0603 on side B, inside the light pipes of the top cover) and hardware mic mute
SW1 pole A lights the red LED, pole B physically disconnects mic data from the CM4 (I2S_DIN grounded) - mute cannot be overridden by software.
Module support: activity LED, 5 V decoupling, rpiboot jumper, debug UART (DNP)

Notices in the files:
README.md:
License:
See [LICENSE](LICENSE). KiCad library parts (symbols, footprints, 3D models under `hardware/3dmodels`) are
CC-BY-SA 4.0 with the KiCad library exception.
